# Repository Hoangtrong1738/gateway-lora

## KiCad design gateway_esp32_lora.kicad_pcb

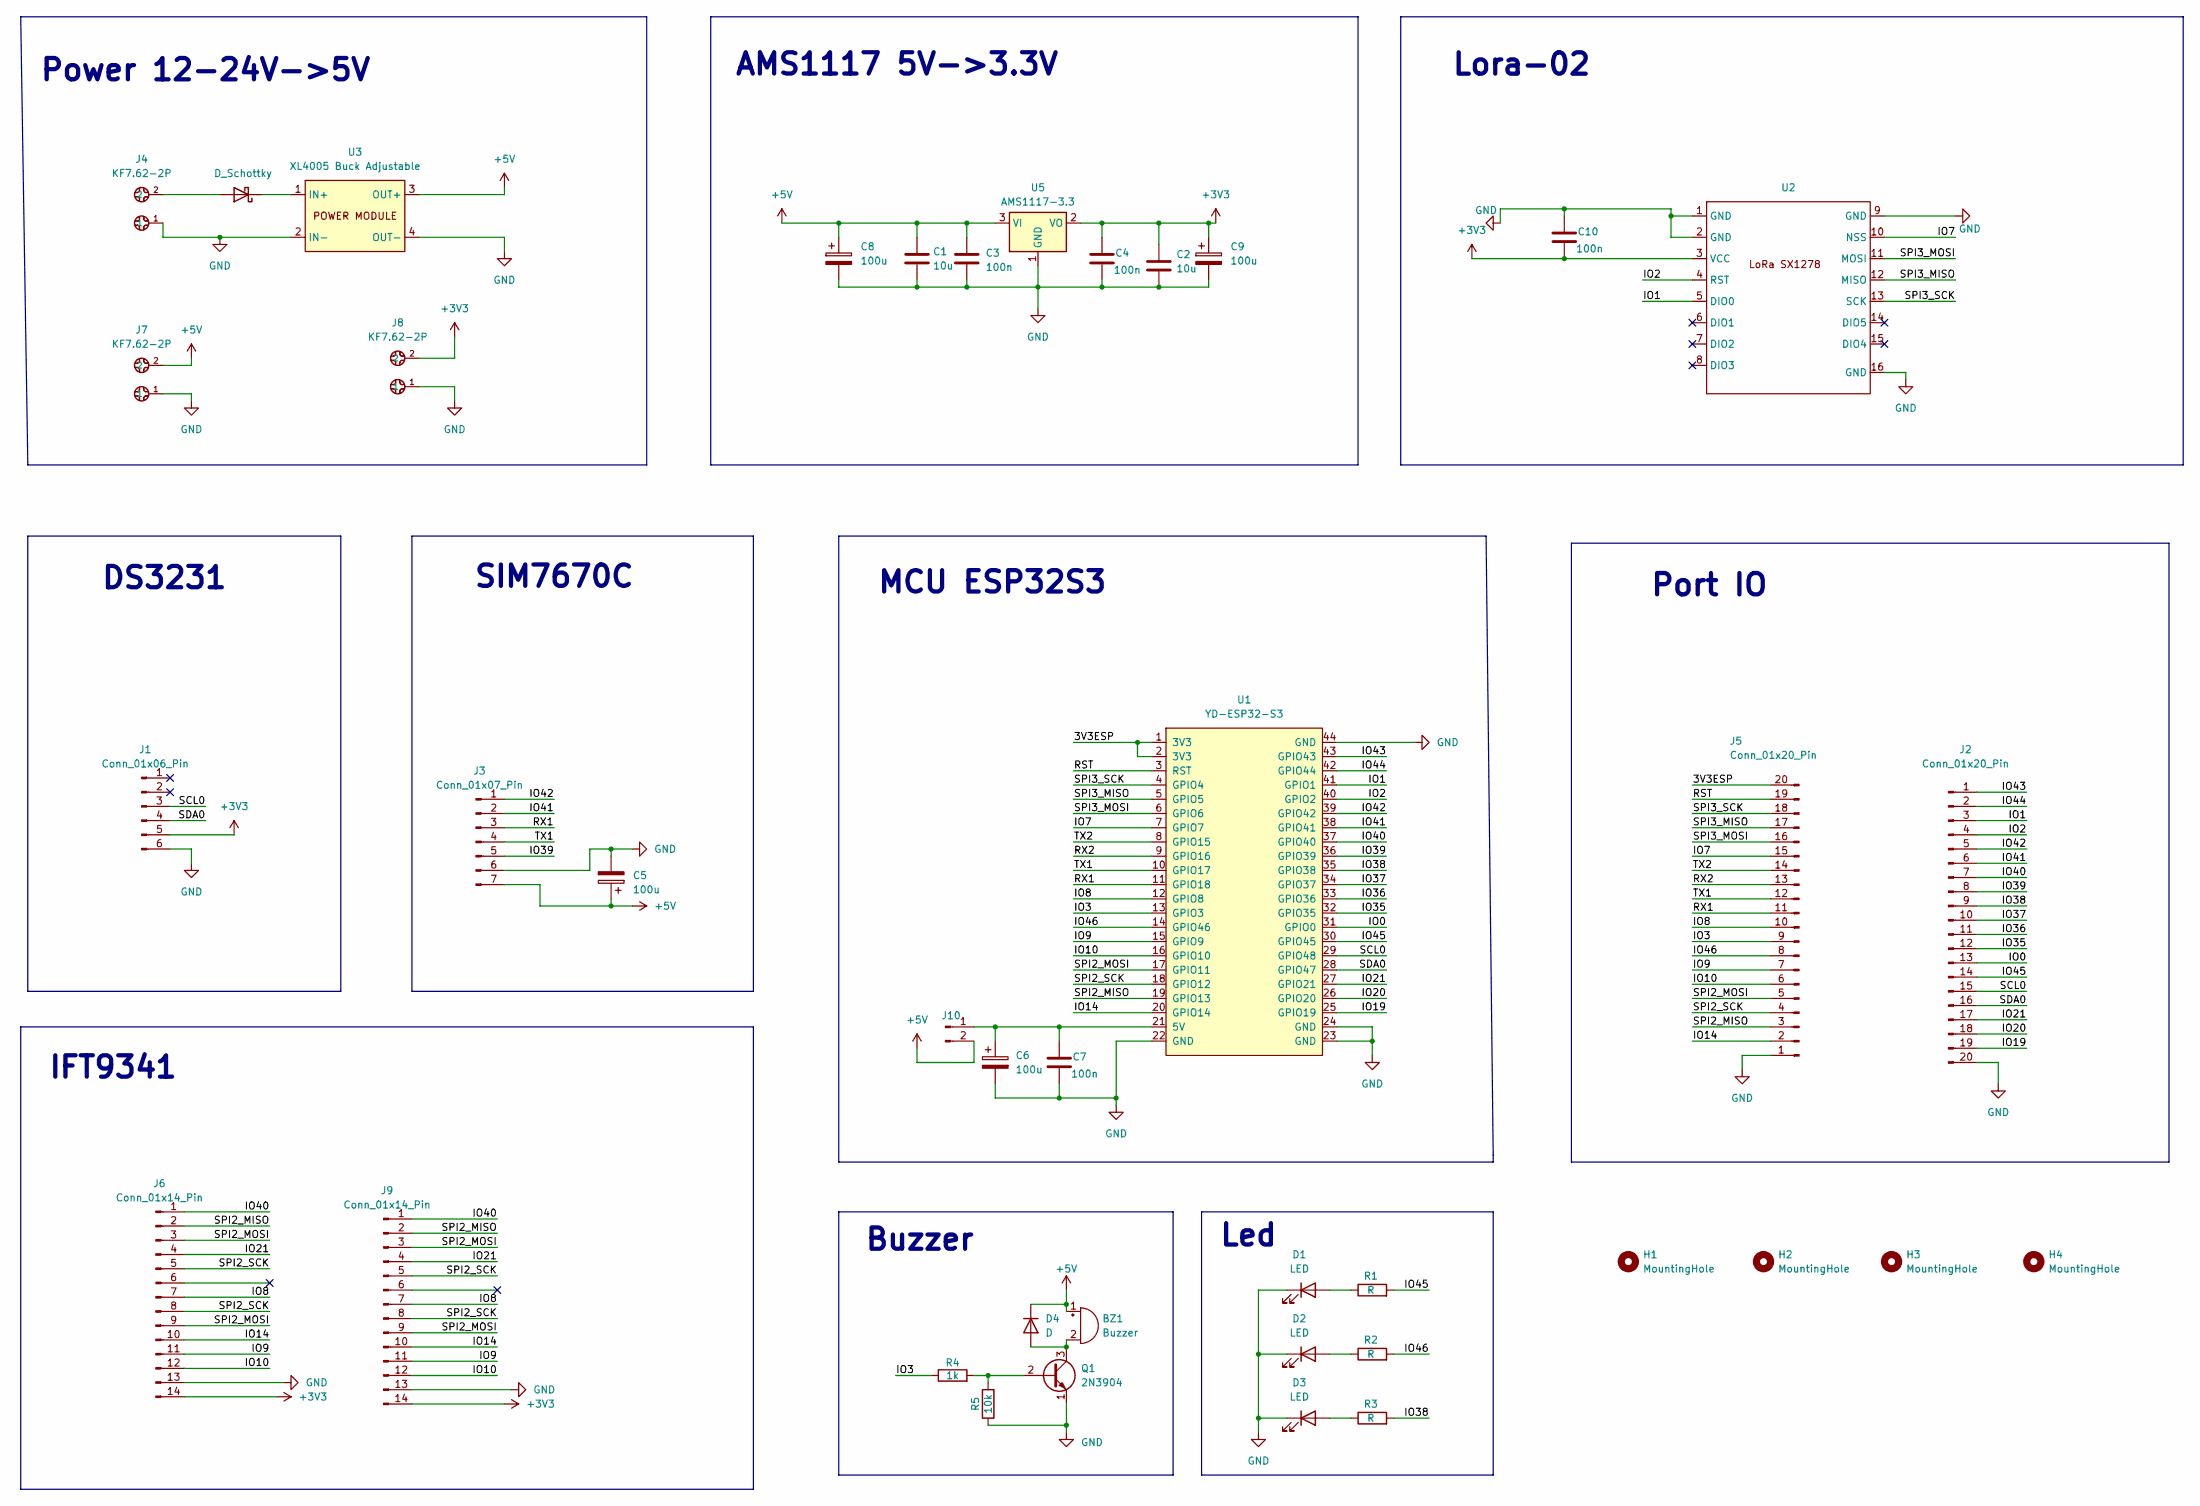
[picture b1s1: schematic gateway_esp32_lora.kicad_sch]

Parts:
BZ1: Buzzer; Buzzer_12x9.5RM7.6
C1, C2: 10u; C_1206_3216Metric
C3, C4, C7, C10: 100n; C_0603_1608Metric
C5, C6: 100u; CP_Radial_D8.0mm_P3.50mm
C8, C9: 100u; CP_Radial_D5.0mm_P2.50mm
D1, D2, D3: LED; LED_0805_2012Metric
D4: D; D_SOD-123
D5: D_Schottky; D_SMA
H1, H2, H3, H4: MountingHole; MountingHole_2.5mm
J1: Conn_01x06_Pin; PinSocket_1x06_P2.54mm_Vertical
J2, J5: Conn_01x20_Pin; PinHeader_1x20_P2.54mm_Vertical
J3: Conn_01x07_Pin; PinSocket_1x07_P2.54mm_Vertical
J4, J7, J8: KF7.62-2P; 2P
J6: Conn_01x14_Pin; JST_XH_B14B-XH-A_1x14_P2.50mm_Vertical
J9: Conn_01x14_Pin; PinSocket_1x14_P2.54mm_Vertical
J10: Conn_01x02_Pin; PinHeader_1x02_P2.54mm_Vertical
Q1: 2N3904; TO-92_Inline
R1, R2, R3: R; R_1206_3216Metric
R4: 1k; R_1206_3216Metric
R5: 10k; R_1206_3216Metric
U1: YD-ESP32-S3; ESP32-S3 modun
U2: LoRa_SX1278
U3: XL4005 Buck Adjustable; MODULE_4P_45x22
U5: AMS1117-3.3; SOT-223-3_TabPin2

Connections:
+3V3: C2.1, C4.1, C9.1, C10.2, J1.5, J6.14, J8.2, J9.14, U2.3 (VCC), U5.2 (VO)
+5V: BZ1.1 (+), C1.1, C3.1, C5.1, C8.1, D4.1 (K), J3.7, J7.2, J10.2, U3.3 (OUT+), U5.3 (VI)
/3V3ESP: J5.20, U1.1 (3V3), U1.2 (3V3)
/IO0: J2.13, U1.31 (GPIO0)
/IO1: J2.3, U1.41 (GPIO1), U2.5 (DIO0)
/IO2: J2.4, U1.40 (GPIO2), U2.4 (RST)
/IO3: J5.9, R4.1, U1.13 (GPIO3)
/IO7: J5.15, U1.7 (GPIO7), U2.10 (NSS)
/IO8: J5.10, J6.7, J9.7, U1.12 (GPIO8)
/IO9: J5.7, J6.11, J9.11, U1.15 (GPIO9)
/IO10: J5.6, J6.12, J9.12, U1.16 (GPIO10)
/IO14: J5.2, J6.10, J9.10, U1.20 (GPIO14)
/IO19: J2.19, U1.25 (GPIO19)
/IO20: J2.18, U1.26 (GPIO20)
/IO21: J2.17, J6.4, J9.4, U1.27 (GPIO21)
/IO35: J2.12, U1.32 (GPIO35)
/IO36: J2.11, U1.33 (GPIO36)
/IO37: J2.10, U1.34 (GPIO37)
/IO38: J2.9, R3.2, U1.35 (GPIO38)
/IO39: J2.8, J3.5, U1.36 (GPIO39)
/IO40: J2.7, J6.1, J9.1, U1.37 (GPIO40)
/IO41: J2.6, J3.2, U1.38 (GPIO41)
/IO42: J2.5, J3.1, U1.39 (GPIO42)
/IO43: J2.1, U1.43 (GPIO43)
/IO44: J2.2, U1.42 (GPIO44)
/IO45: J2.14, R1.2, U1.30 (GPIO45)
/IO46: J5.8, R2.2, U1.14 (GPIO46)
/RST: J5.19, U1.3 (RST)
/RX1: J3.3, J5.11, U1.11 (GPIO18)
/RX2: J5.13, U1.9 (GPIO16)
/SCL0: J1.3, J2.15, U1.29 (GPIO48)
/SDA0: J1.4, J2.16, U1.28 (GPIO47)
/SPI2_MISO: J5.3, J6.2, J9.2, U1.19 (GPIO13)
/SPI2_MOSI: J5.5, J6.3, J6.9, J9.3, J9.9, U1.17 (GPIO11)
/SPI2_SCK: J5.4, J6.5, J6.8, J9.5, J9.8, U1.18 (GPIO12)
/SPI3_MISO: J5.17, U1.5 (GPIO5), U2.12 (MISO)
/SPI3_MOSI: J5.16, U1.6 (GPIO6), U2.11 (MOSI)
/SPI3_SCK: J5.18, U1.4 (GPIO4), U2.13 (SCK)
/TX1: J3.4, J5.12, U1.10 (GPIO17)
/TX2: J5.14, U1.8 (GPIO15)
GND: C1.2, C2.2, C3.2, C4.2, C5.2, C6.2, C7.2, C8.2, C9.2, C10.1, D1.1 (K), D2.1 (K), D3.1 (K), J1.6, J2.20, J3.6, J4.1, J5.1, J6.13, J7.1, J8.1, J9.13, Q1.1 (E), R5.1, U1.22 (GND), U1.23 (GND), U1.24 (GND), U1.44 (GND), U2.1 (GND), U2.2 (GND), U2.9 (GND), U2.16 (GND), U3.2 (IN-), U3.4 (OUT-), U5.1 (GND)
unnamed: BZ1.2 (-), D4.2 (A), Q1.3 (C)
unnamed: D1.2 (A), R1.1
unnamed: D2.2 (A), R2.1
unnamed: D3.2 (A), R3.1
unnamed: D5.2 (A), J4.2
unnamed: D5.1 (K), U3.1 (IN+)
unnamed: C6.1, C7.1, J10.1, U1.21 (5V)
unnamed: Q1.2 (B), R4.2, R5.2

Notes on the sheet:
Power 12-24V->5V
Led
Buzzer
DS3231
Lora-02
MCU ESP32S3
IFT9341
Port IO
AMS1117 5V->3.3V
SIM7670C

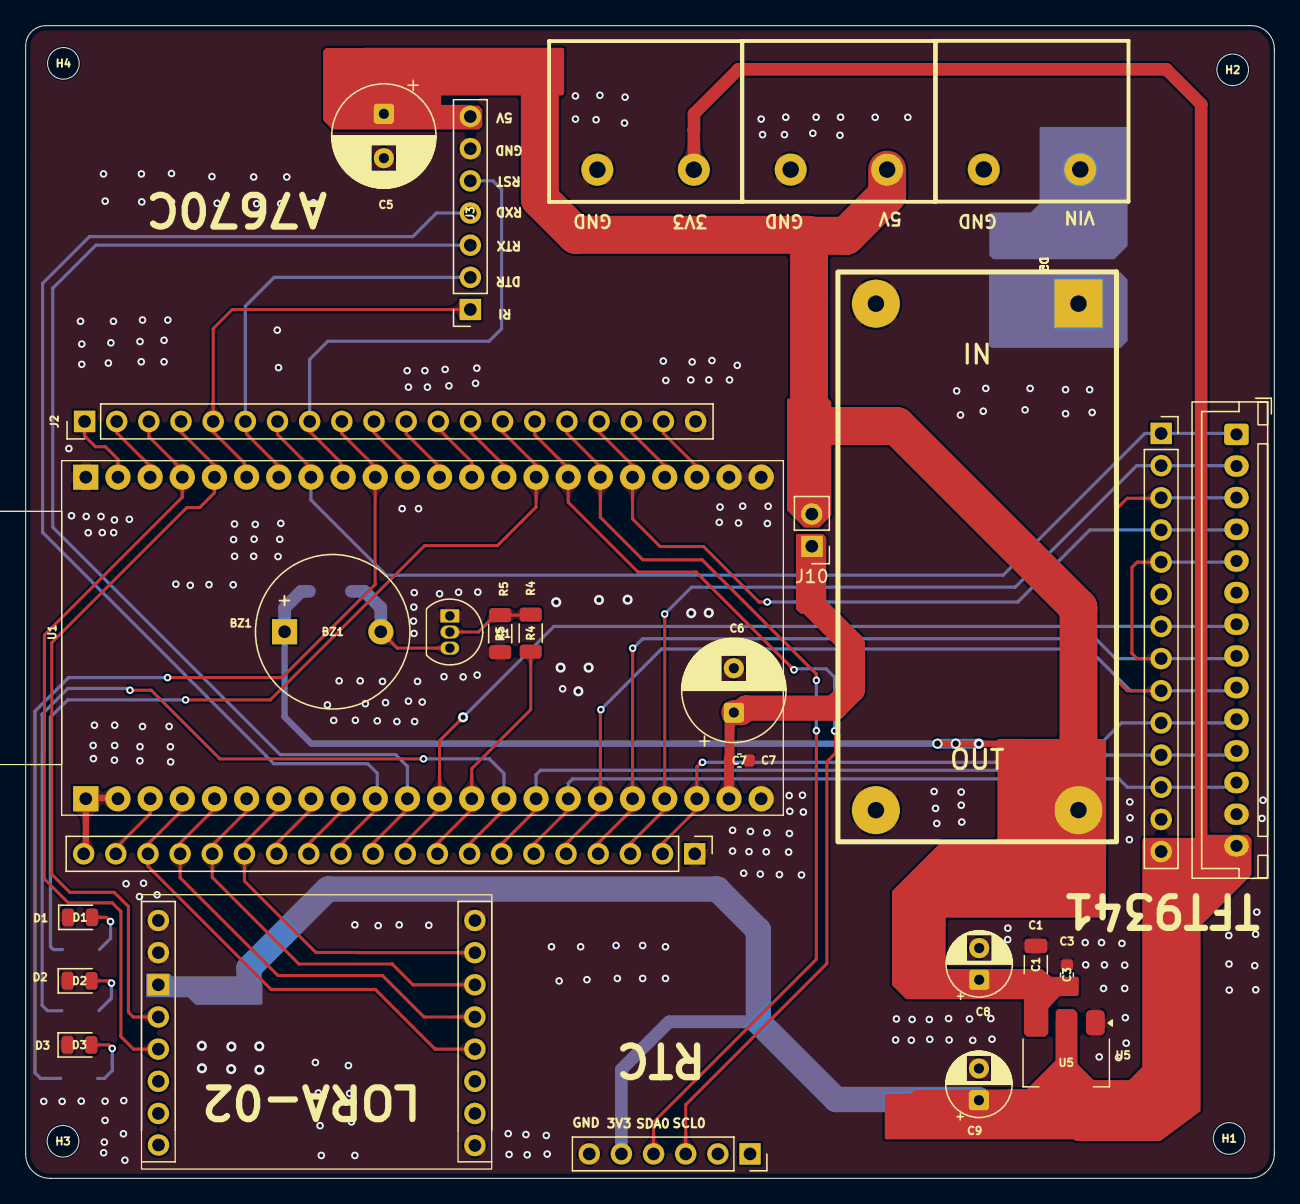
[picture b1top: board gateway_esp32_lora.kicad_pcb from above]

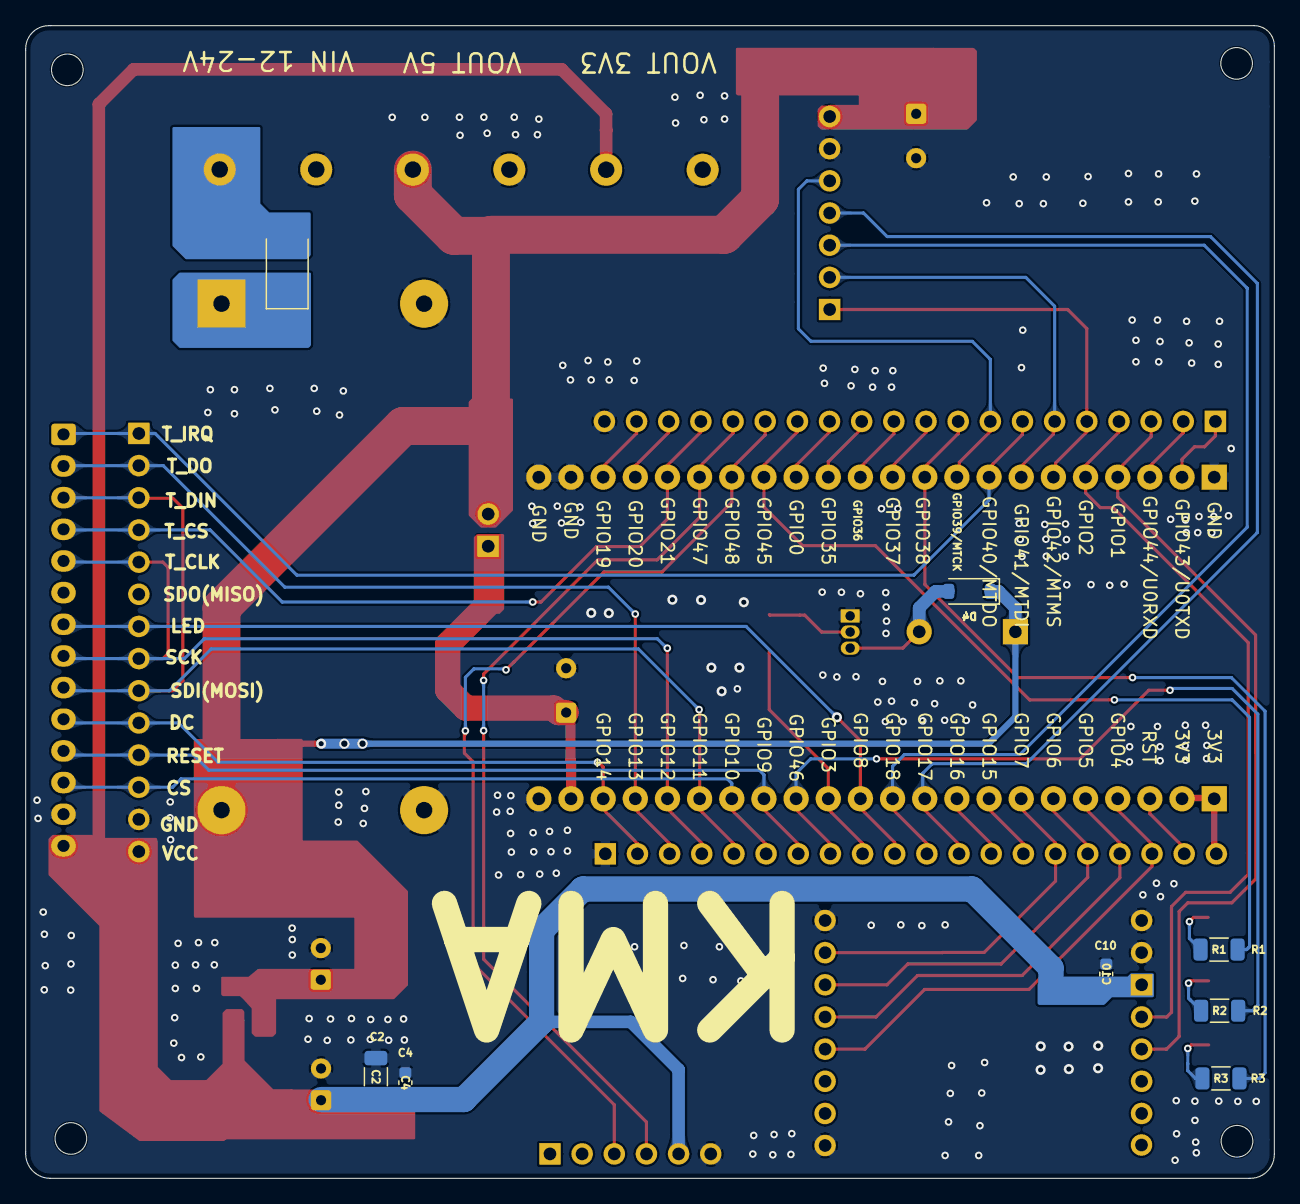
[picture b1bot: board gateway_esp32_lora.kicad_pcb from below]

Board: 2 copper layers, 98.6 x 91.0 mm, 40 parts (8 on the bottom side), 49 nets.
